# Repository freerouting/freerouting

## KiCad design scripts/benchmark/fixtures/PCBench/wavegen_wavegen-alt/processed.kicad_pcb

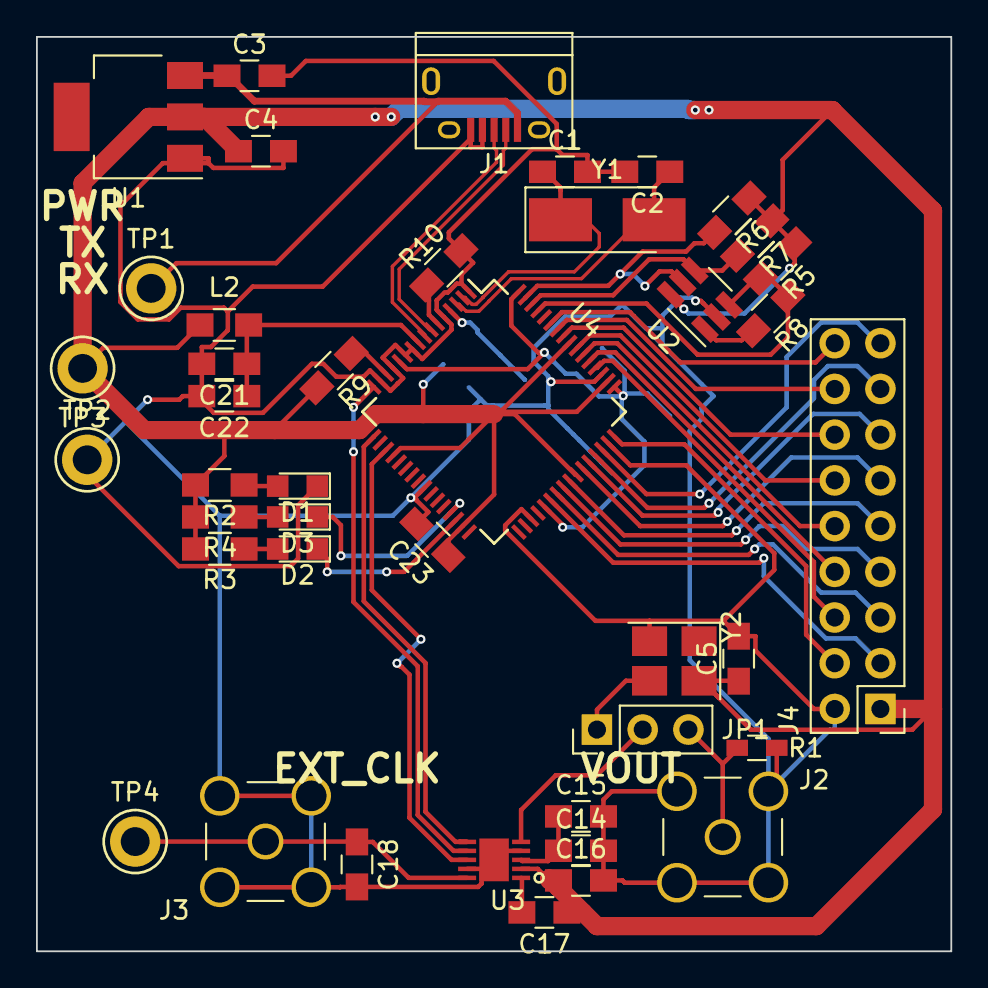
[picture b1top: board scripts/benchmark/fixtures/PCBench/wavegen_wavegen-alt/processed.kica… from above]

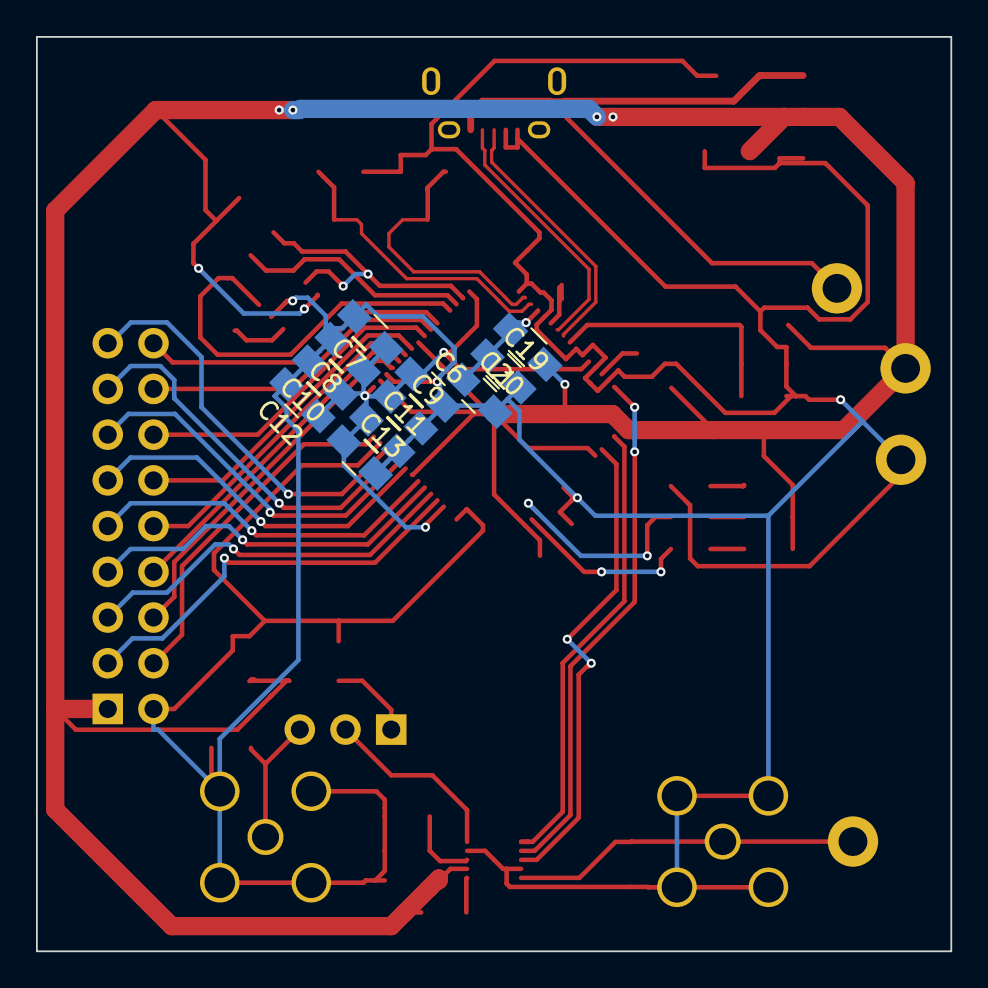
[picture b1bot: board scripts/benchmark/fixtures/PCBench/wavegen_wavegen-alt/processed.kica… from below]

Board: 2 copper layers, 50.8 x 50.8 mm, 53 parts (11 on the bottom side), 46 nets.

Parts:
C1, C2: 27p; C_0805_HandSoldering
C3, C5, C7, C8, C9, C10, C11, C12, C13, C14, C16, C18, C20, C22, C23: 100n; C_0805_HandSoldering
C4, C15: 10u; C_0805_HandSoldering
C6: 3.3u; C_0805_HandSoldering
C17: 10n; C_0805_HandSoldering
C19, C21: 4.7u; C_0805_HandSoldering
D1, D2, D3: LED_Small; LED_0805
J1: USB_B; USB_Micro-B
J2: EXT_CLK; SMA_THT_Jack_Straight
J3: VOUT; SMA_THT_Jack_Straight
J4: CONN_02X09; Pin_Header_Straight_2x09_Pitch2.54mm
JP1: CLK_SELECT; Pin_Header_Straight_1x03_Pitch2.54mm
L1, L2: 800m; L_0805_HandSoldering
R1: 50; R_0603_HandSoldering
R2, R3, R4: 470; R_0805_HandSoldering
R5, R6, R7: 10k; R_0805_HandSoldering
R8: 2.2k; R_0805_HandSoldering
R9: 1k; R_0805_HandSoldering
R10: 12k; R_0805_HandSoldering
TP1: VBUS; Test_Point_Keystone_5005-5009_Compact
TP2: GND; Test_Point_Keystone_5005-5009_Compact
TP3: +3.3V; Test_Point_Keystone_5005-5009_Compact
TP4: VOUT; Test_Point_Keystone_5005-5009_Compact
U1: LD1117S33TR; SOT-223
U2: 93LC46BT; SOT-23-6_Handsoldering
U3: AD9837
U4: FT2232H; LQFP-64_10x10mm_Pitch0.5mm
Y1: 12MHz; Crystal_SMD_5032-2pin_5.0x3.2mm_HandSoldering
Y2: OXETGCJANF; Oscillator_SMD_Abracon_ASE-4pin_3.2x2.5mm_HandSoldering

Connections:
+3V3: C4.1, C5.1, C16.1, C17.1, C23.1, J4.1, L1.1, L2.1, R2.2, R3.2, R4.2, R5.1, R6.1, R7.1, R9.2, TP3.1, U1.2, U2.6, U3.2, U4.20, U4.31, U4.42, U4.50, U4.56, Y2.4
/SCK: U3.7, U4.16
/SDATA: U3.6, U4.17
/~FSYNC: U3.8, U4.19
DAC_CLK: JP1.2, U3.5
EECLK: R7.2, U2.4, U4.62
EECS: R6.2, U2.5, U4.63
EEDATA: R5.2, R8.1, U2.3, U4.61
FTOSC+: C2.1, U4.3, Y1.2
FTOSC-: C1.1, U4.2, Y1.1
FTRXLED: D3.1, U4.29
FTTXLED: D2.1, U4.30
FTVPHY: C19.1, C20.1, L1.2, U4.4
FTVPLL: C21.1, C22.1, L2.2, U4.9
GNDA: C1.2, C2.2, C3.2, C4.2, C5.2, C6.2, C7.2, C8.2, C9.2, C10.2, C11.2, C12.2, C13.2, C14.2, C15.2, C16.2, C18.2, C19.2, C20.2, C21.2, C22.2, C23.2, D1.1, J1.4, J1.5, J2.2, J3.2, J4.2, R1.2, R10.2, TP2.1, U1.1, U2.2, U3.4, U3.9, U3.11, U4.1, U4.5, U4.10, U4.11, U4.13, U4.15, U4.25, U4.35, U4.47, U4.51, Y2.2
unnamed: C3.1, J1.1, TP1.1, U1.3
unnamed: C6.1, C7.1, C8.1, C9.1, C10.1, C11.1, C12.1, C13.1, U4.12, U4.37, U4.49, U4.64
unnamed: C14.1, C15.1, U3.3
unnamed: C17.2, U3.1
unnamed: C18.1, J3.1, TP4.1, U3.10
unnamed: D1.2, R2.1
unnamed: D2.2, R3.1
unnamed: D3.2, R4.1
unnamed: J2.1, JP1.3, R1.1
unnamed: J4.3, U4.38
unnamed: J4.4, U4.48
unnamed: J4.5, U4.39
unnamed: J4.6, U4.52
unnamed: J4.7, U4.40
unnamed: J4.8, U4.53
unnamed: J4.9, U4.41
unnamed: J4.10, U4.54
unnamed: J4.11, U4.43
unnamed: J4.12, U4.55
unnamed: J4.13, U4.44
unnamed: J4.14, U4.57
unnamed: J4.15, U4.45
unnamed: J4.16, U4.58
unnamed: J4.17, U4.46
unnamed: J4.18, U4.59
unnamed: JP1.1, Y2.3
unnamed: R8.2, U2.1
unnamed: R9.1, U4.14
unnamed: R10.1, U4.6
USB_D+: J1.3, U4.8
USB_D-: J1.2, U4.7

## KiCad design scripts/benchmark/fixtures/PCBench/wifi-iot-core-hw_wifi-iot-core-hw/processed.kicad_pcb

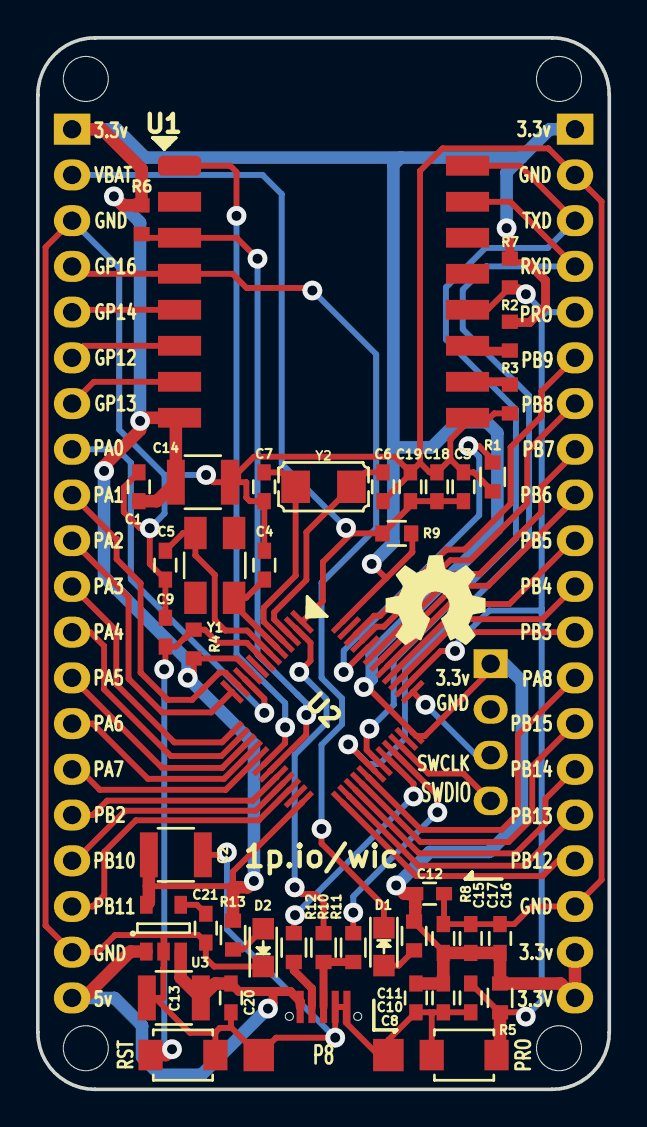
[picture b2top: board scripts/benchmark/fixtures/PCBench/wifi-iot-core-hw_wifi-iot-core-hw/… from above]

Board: 2 copper layers, 31.8 x 58.4 mm, 52 parts (0 on the bottom side), 54 nets.

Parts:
C1, C9, C10, C11, C12, C15, C17, C19, C20: 0.1uF; C_0603
C2, C13, C14: 10uF-50v; C_1210
C3: 100nF; C_0603
C4, C5: 10pF; C_0603
C6: 15pF; C_0603
C7: 15pf; C_0603
C8: 470pF; C_0603
C16, C18: 1uF; C_0603
C21: 10nF; C_0603
D1: Led GPIO16; LED_0805
D2: Led; LED_0805
P1, P2: CONN_01X20; Pin_Header_Straight_1x20
P3, P4, P5, P6: CONN_01X01; MountingHole_2.5mm
P7: CONN_01X04; Pin_Header_Straight_1x04
P8: USB; Micro_usb_B_smd
PRO: SW_PUSH_SMALL_H; SW_SPST_B3U-1000P-B
R1, R6, R7, R8, R13: 10k; R_0603
R2, R3, R4, R5: 10K; R_0603
R9: 0R; R_0603
R10: 1.5K; R_0603
R11, R12: 22; R_0603
RST: RST; SW_SPST_B3U-1000P-B
U1: ESP-07v2; ESP-07v2-smd-16pin
U2: STM32F103C8Tx; LQFP-48_Pin1.7x0.3mm_Pitch0.5mm
U3: LP2985LV; SOT-23-5
VAL**: oshw_logo_500; logo5
Y1: 8MHz; Crystal_SMD_5032_4Pads
Y2: 32.687; crystal_smd_32.768_2Pin

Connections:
+3V3: C1.1, C2.1, C10.2, C11.2, C12.1, C14.1, C15.2, C16.2, C17.2, P1.1, P2.1, P2.19, P2.20, P7.1, R2.1, R4.2, R5.2, R6.1, R7.1, R8.1, R9.2, R13.1, U1.8, U2.9, U2.24, U2.36, U2.48, U3.5
+5V: C13.1, C20.1, P1.20, P8.1, U3.1, U3.3
/CH_PD: R6.2, U1.3, U2.19
/ESP_PRO: C8.1, P2.5, PRO.1, R5.1, R7.2, U1.12, U2.38
/ESP_RST: U1.1, U2.18
/ESP_RXD: P2.4, U1.15, U2.30
/ESP_TXD: P2.3, U1.16, U2.31
/GPIO16: D1.1, P1.4, U1.4
/RST: C9.1, R4.1, RST.1, U2.7
/SWCLK: P7.3, U2.37
/SWDIO: P7.4, U2.34
/USB_DIS: R10.1, U2.2
/USB_DM: R12.1, U2.32
/USB_DP: R11.1, U2.33
/VBAT: C3.2, C18.2, C19.2, P1.2, R9.1, U2.1
GNDREF: C1.2, C2.2, C3.1, C4.2, C5.2, C6.2, C7.2, C8.2, C9.2, C10.1, C11.1, C12.2, C13.2, C14.2, C15.1, C16.1, C17.1, C18.1, C19.1, C20.2, C21.2, D2.1, P1.3, P1.19, P2.2, P2.18, P8.4, P8.5, PRO.2, R1.2, R3.2, RST.2, U1.9, U3.2
GPIO12: P1.6, U1.6
GPIO13: P1.7, U1.7
GPIO14: P1.5, U1.5
unnamed: C4.1, U2.5, Y1.1
unnamed: C5.1, U2.6, Y1.2
unnamed: C6.1, U2.3, Y2.1
unnamed: C7.1, U2.4, Y2.2
unnamed: C21.1, U3.4
unnamed: D1.2, R8.2
unnamed: D2.2, R13.2
unnamed: P8.2, R12.2
unnamed: P8.3, R10.2, R11.2
unnamed: R1.1, U2.44
unnamed: R2.2, U1.11
unnamed: R3.1, U1.10
PA0: P1.8, U2.10
PA1: P1.9, U2.11
PA2: P1.10, U2.12
PA3: P1.11, U2.13
PA4: P1.12, U2.14
PA5: P1.13, U2.15
PA6: P1.14, U2.16
PA7: P1.15, U2.17
PA8: P2.13, U2.29
PB2: P1.16, U2.20
PB3: P2.12, U2.39
PB4: P2.11, U2.40
PB5: P2.10, U2.41
PB6: P2.9, U2.42
PB7: P2.8, U2.43
PB8: P2.7, U2.45
PB9: P2.6, U2.46
PB10: P1.17, U2.21
PB11: P1.18, U2.22
PB12: P2.17, U2.25
PB13: P2.16, U2.26
PB14: P2.15, U2.27
PB15: P2.14, U2.28
